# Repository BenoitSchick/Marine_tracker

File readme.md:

# 🌊 PI MONIT – Group 4  
## Marine Animal Tracking System  

**Schick Benoit · Warpelin Daryl · Jeyapalan Jeyapiragash · Zweifel Robin**

---

## 📌 Project Overview

This project focuses on the design of an embedded tracking module intended to be attached to marine animals.

The primary objective is to monitor animal movements in order to:

- Better understand behavioural patterns  
- Analyse migratory routes  
- Identify critical marine areas requiring protection  

Beyond behavioural research, marine animals provide a unique and valuable platform for carrying environmental sensors. Their ability to travel long distances and dive to great depths enables data collection in regions that are difficult — or impossible — for humans to access.

Our system is designed to measure **ocean temperature as a function of depth**, contributing to climate research. Ocean temperature plays a crucial role in regulating ocean currents, which in turn significantly influence the planet’s global thermal balance.

The device must satisfy both **animal tracking** and **oceanographic measurement** requirements, while operating reliably under extreme marine conditions.

---

## 🌊 Mechanical & Environmental Constraints

The module must withstand harsh deep-sea conditions for extended periods.

### Pressure Resistance

- Fully waterproof housing  
- Designed to resist pressures equivalent to **1,000 m depth** (to be confirmed)  
- Some marine species dive beyond 1,000 m  

### Corrosion & Environmental Resistance

- Long-term exposure to seawater  
- Resistance to:
  - Salinity  
  - Thermal variations  
  - Biological fouling  

### Duration

- Minimum operational lifespan: **1 month**  
- Corresponds to a typical migration cycle  

### Structural Integrity

- Housing must maintain mechanical integrity despite:
  - High pressure  
  - Temperature changes  
  - Continuous environmental stress  

---

## ⚡ Electronic Constraints & Specifications

The embedded system must operate autonomously for at least **one month**.

### Power Optimization Strategy

- Optimised electronic architecture  
- Deep sleep operating modes  
- Careful selection of ultra-low-power components  

### Required Sensors

The module must integrate:

- 🌡️ **Temperature sensor**  
- 📏 **Pressure sensor** (for depth measurement and data validation)

These measurements form the foundation of the ocean monitoring component of the project.

---

## 📍 Localisation System

A GPS module must be integrated to:

- Track the animal’s position  
- Associate environmental measurements with precise geographic coordinates  

Position data is essential for accurate mapping and scientific analysis.

---

## 📡 Data Communication

When the animal surfaces, the module must transmit collected data.

Because the system operates in open ocean environments, communication must be achieved via:

- 🛰️ **Satellite link** (global coverage solution)

The transmitted data is then:

- Stored in a central database  
- Prepared for processing and analysis  

---

## 📊 Data Processing & Visualisation

Collected data will be:

1. Processed and validated  
2. Made accessible via a web platform  
3. Presented through interactive visualisations  

The platform must also:

- Provide access to raw scientific data  
- Enable collaboration within the research community  

The final repository could be based on the EMODnet portal  
(European Marine Observation and Data Network).

---

## 🎯 Project Goals Summary

- ✔ Long-term autonomous marine monitoring  
- ✔ Behavioural tracking of marine species  
- ✔ Ocean temperature profiling by depth  
- ✔ Satellite-based data transmission  
- ✔ Open scientific data access  
- ✔ Contribution to climate research  

---

> PI MONIT aims to combine embedded systems engineering, oceanography, and data science to support marine conservation and climate research.

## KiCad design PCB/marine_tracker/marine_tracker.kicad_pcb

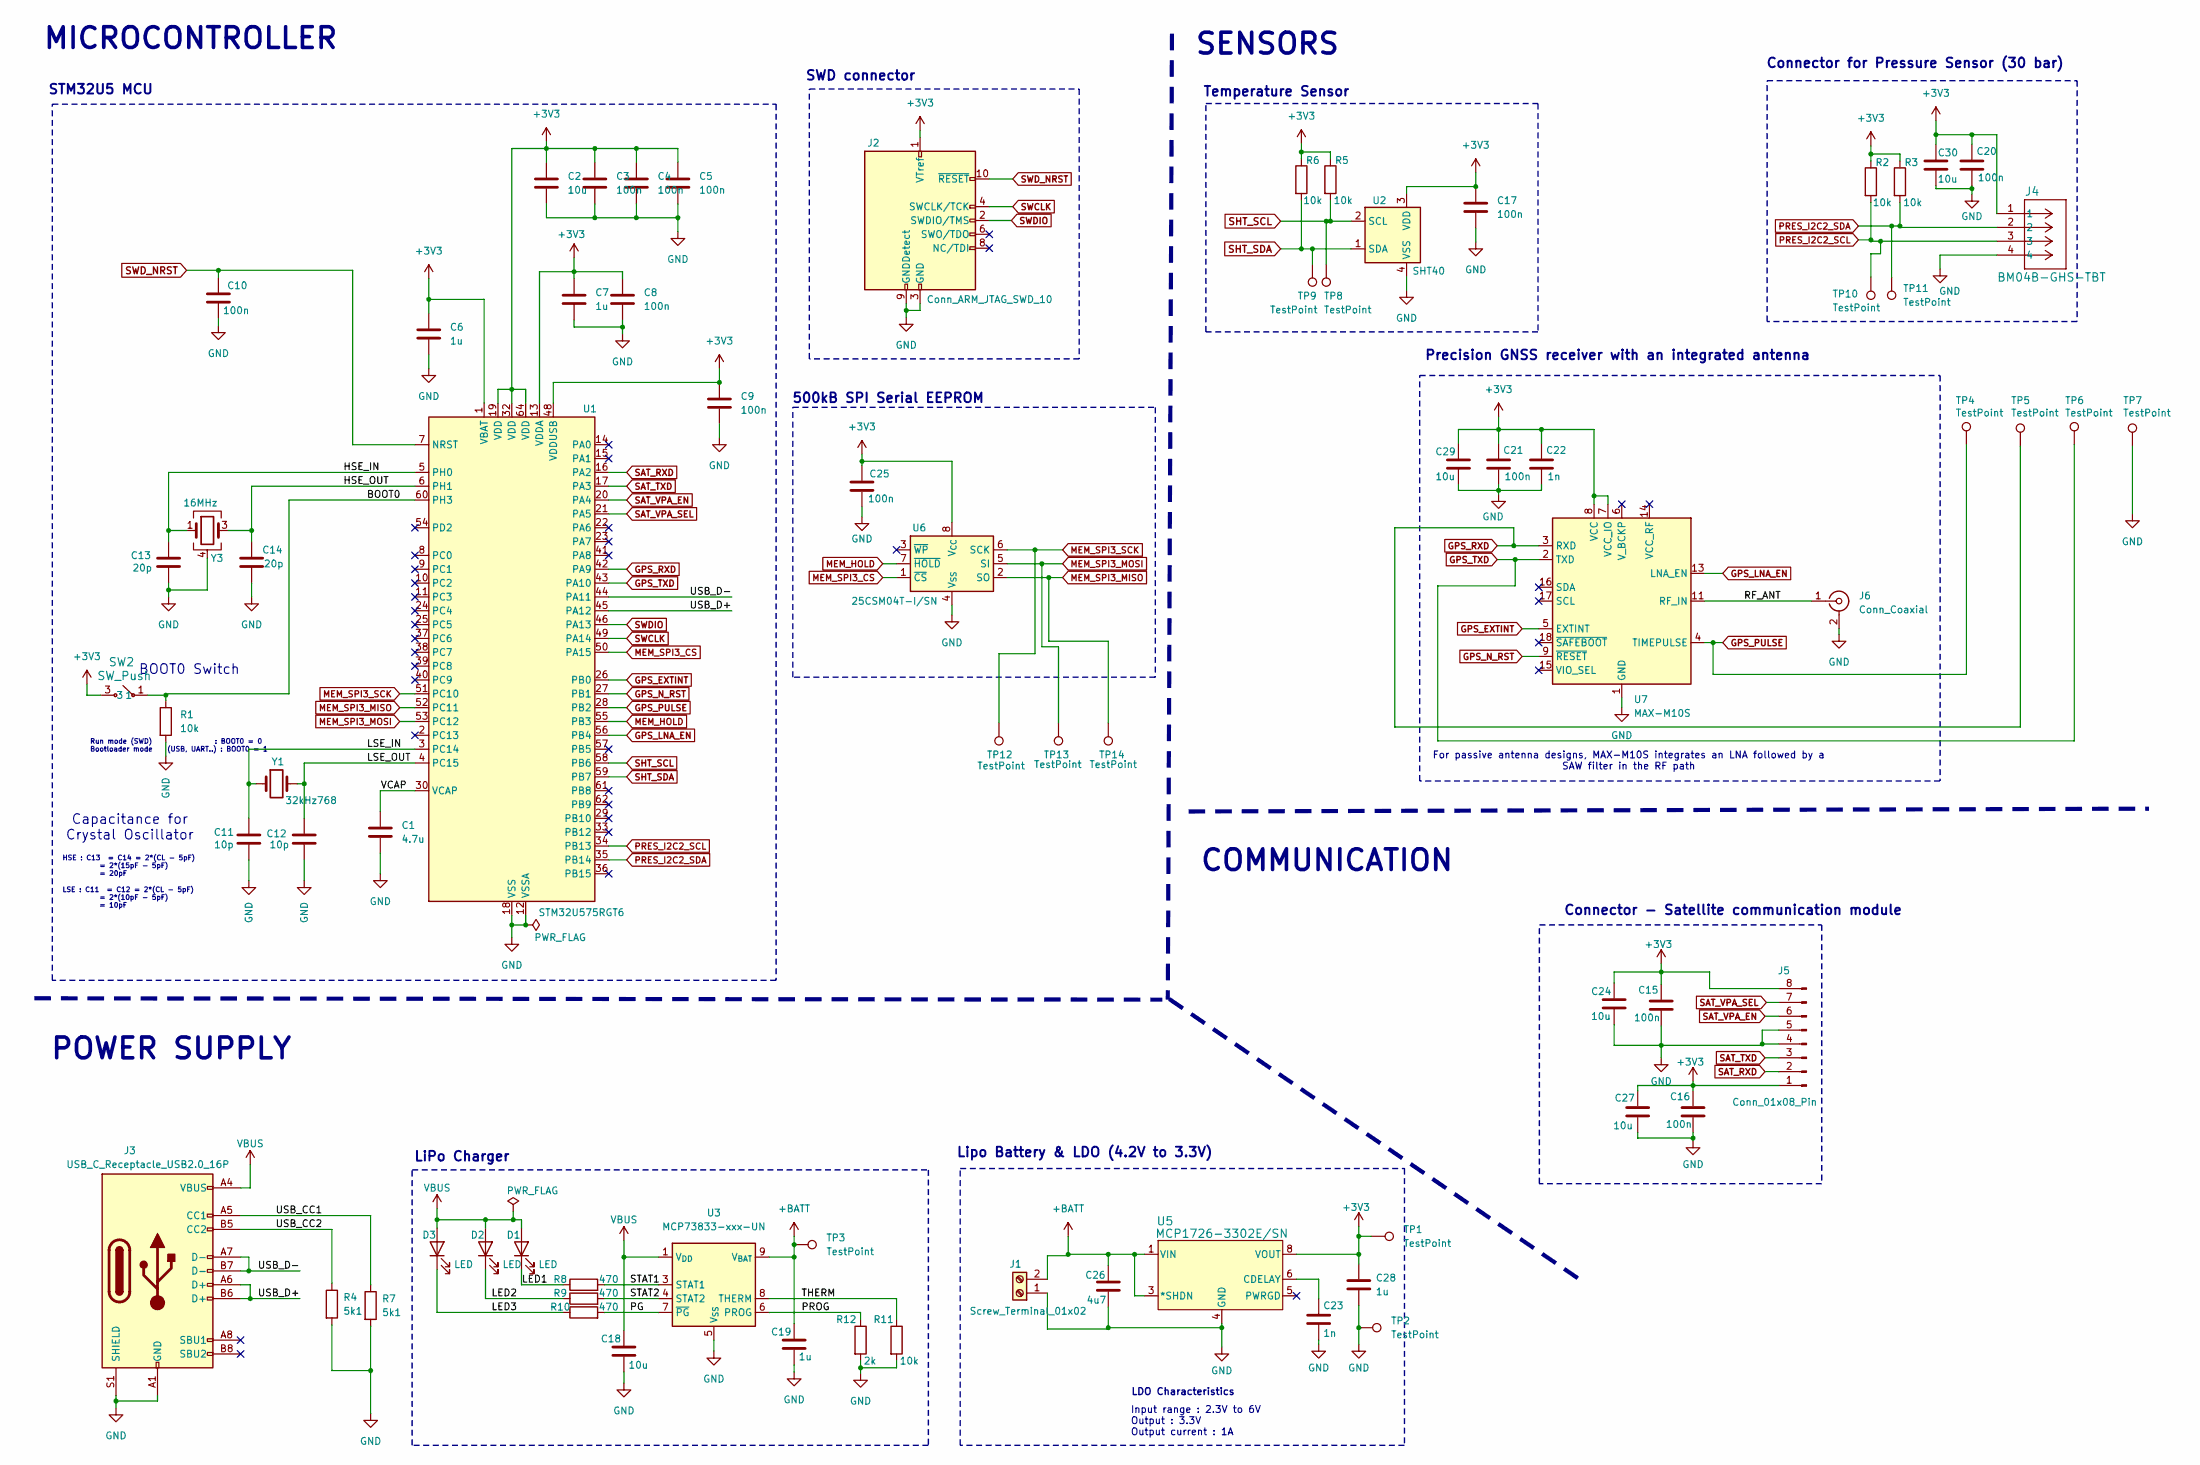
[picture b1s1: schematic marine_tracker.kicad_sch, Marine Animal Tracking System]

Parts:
C1: 4.7u; C_0805_2012Metric; Manufacturer Part Number CC0805ZKY5V7BB475; Digikey Part Number 311-1907-2-ND
C2, C18, C24, C27, C29, C30: 10u; C_0805_2012Metric; Manufacturer Part Number CC0805KRX5R7BB106; Digikey Part Number 311-3502-2-ND
C3, C4, C5, C8, C9, C10, C15, C16, C17, C20, C21, C25: 100n; C_0603_1608Metric; Manufacturer Part Number CC0603KRX7R7BB104; Digikey Part Number 311-1088-2-ND
C6, C7, C19, C28: 1u; C_0603_1608Metric; Manufacturer Part Number CC0603KRX7R7BB105; Digikey Part Number 311-1446-2-ND
C11, C12: 10p; C_0603_1608Metric; Manufacturer Part Number CC0603JRNPO9BN100; Digikey Part Number 311-1058-2-ND
C13, C14: 20p; C_0603_1608Metric; Manufacturer Part Number CC0603JRNPO0BN200; Digikey Part Number 311-1754-2-ND
C22, C23: 1n; C_0603_1608Metric; Manufacturer Part Number CC0603JPNPO9BN102; Digikey Part Number 13-CC0603JPNPO9BN102TR-ND
C26: 4u7; C_0603_1608Metric; Manufacturer Part Number CC0603KRX5R7BB475; Digikey Part Number 311-1785-2-ND
D1, D2, D3: LED; LED_0603_1608Metric; Manufacturer Part Number SML-D12U1WT86; Digikey Part Number SML-D12U1WT86TR-ND
J1: Screw_Terminal_01x02; Screw_terminal_1x2; Manufacturer Part Number 691137710002; Digikey Part Number 732-10955-ND
J2: Conn_ARM_JTAG_SWD_10; PinHeader_2x05_P1.27mm_Vertical; Manufacturer Part Number 20021111-00010T4LF; Digikey Part Number 609-3712-ND
J3: USB_C_Receptacle_USB2.0_16P; USB_C_Receptacle_GCT_USB4105-xx-A_16P_TopMnt_Horizontal; Manufacturer Part Number USB4215-03-A; Digikey Part Number 2073-USB4215-03-ATR-ND
J4: BM04B-GHS-TBT; CONN_BM04B-GHS-TBT_JST; Manufacturer Part Number BM04B-GHS-TBT; Digikey Part Number 455-BM04B-GHS-TBTTR-ND
J5: Conn_01x08_Pin; PinHeader_1x08_P2.54mm_Vertical; Manufacturer Part Number 61300811121; Digikey Part Number 732-5321-ND
J6: Conn_Coaxial; CONN_UFL_RSP-122811-01_SAI; Manufacturer Part Number RSP-122811-01; Digikey Part Number 612-RSP-122811-01TR-ND
R1, R2, R3, R5, R6, R11: 10k; R_0402_1005Metric; Manufacturer Part Number RC0402FR-0710KL; Digikey Part Number 311-10.0KLRTR-ND
R4, R7: 5k1; R_0402_1005Metric; Manufacturer Part Number RC0402FR-075K1L; Digikey Part Number 311-5.10KLRTR-ND
R8, R9, R10: 470; R_0402_1005Metric; Manufacturer Part Number RC0402FR-07470RL; Digikey Part Number 311-470LRTR-ND
R12: 2k; R_0402_1005Metric; Manufacturer Part Number RC0402FR-072KL; Digikey Part Number 311-2KLRTR-ND
SW2: SW_Push; SW4_PTS815 SJM 250 SMTR LFS_CNK_btnPoussoir; Manufacturer Part Number PTS815SJM250SMTRLFS; Digikey Part Number CKN12215-2-ND
TP1, TP2, TP3, TP8, TP9, TP12, TP13, TP14: TestPoint; TestPoint_Pad_D1.0mm
TP4, TP5, TP6, TP7, TP10, TP11: TestPoint; PinHeader_1x01_P2.54mm_Vertical
U1: STM32U575RGT6; LQFP-64_10x10mm_P0.5mm; Manufacturer Part Number STM32U575RGT6; Digikey Part Number 497-STM32U575RGT6-ND
U2: SHT40; Sensirion_DFN-4_1.5x1.5mm_P0.8mm_SHT4x_NoCentralPad; Manufacturer Part Number SHT40-AD1B-R3; Digikey Part Number 1649-SHT40-AD1B-R3TR-ND
U3: MCP73833-xxx-UN; lipo_charger; Manufacturer Part Number MCP73833T-FCI/MF; Digikey Part Number MCP73833T-FCI/MFTR-ND
U5: MCP1726-3302E/SN; LDO_1A; Manufacturer Part Number MCP1726-3302E/MF; Digikey Part Number MCP1726-3302E/MF-ND
U6: 25CSM04T-I/SN; JEITA_SOIC-8_3.9x4.9mm_P1.27mm; Manufacturer Part Number 25CSM04T-I/SN; Digikey Part Number 150-25CSM04T-I/SNTR-ND
U7: MAX-M10S; ublox_MAX; Manufacturer Part Number MAX-M10S-00B; Digikey Part Number 672-MAX-M10S-00BTR-ND
Y1: 32kHz768; Crystal_SMD_3215-2Pin_3.2x1.5mm; Manufacturer Part Number FC-135R 32.7680KA-A3; Digikey Part Number SER4071TR-ND
Y3: 16MHz; Crystal_SMD_5032-4Pin_5.0x3.2mm; Manufacturer Part Number X1G0044510002; Digikey Part Number SER4396TR-ND

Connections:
+3V3: C2.1, C3.1, C4.1, C5.1, C6.1, C7.1, C8.1, C9.1, C15.1, C16.1, C17.1, C20.1, C21.1, C22.1, C24.1, C25.1, C27.1, C28.1, C29.1, C30.1, J2.1 (VTref), J4.1, J5.1, J5.8, R2.1, R3.1, R5.1, R6.1, SW2.3, SW2.4, TP1.1, U1.1 (VBAT), U1.13 (VDDA), U1.19 (VDD), U1.32 (VDD), U1.48 (VDDUSB), U1.64 (VDD), U2.3 (VDD), U5.7 (VOUT), U5.8 (VOUT), U6.8 (V_{CC}), U7.7 (VCC_IO), U7.8 (VCC)
+BATT: C19.1, C26.1, J1.2, TP3.1, U3.9 (V_{BAT}), U3.10 (V_{BAT}), U5.1 (VIN), U5.2 (VIN), U5.3 (*SHDN)
/BOOT0: R1.1, SW2.1, SW2.2, U1.60 (PH3)
/HSE_IN: C13.2, U1.5 (PH0), Y3.1
/HSE_OUT: C14.2, U1.6 (PH1), Y3.3
/LED1: D1.1 (K), R8.1
/LED2: D2.1 (K), R9.1
/LED3: D3.1 (K), R10.1
/LSE_IN: C11.2, U1.3 (PC14), Y1.1
/LSE_OUT: C12.2, U1.4 (PC15), Y1.2
/PG: R10.2, U3.7 (~PG)
/PROG: R12.1, U3.6 (PROG)
/RF_ANT: J6.1 (In), U7.11 (RF_IN)
/STAT1: R8.2, U3.3 (STAT1)
/STAT2: R9.2, U3.4 (STAT2)
/THERM: R11.1, U3.8 (THERM)
/USB_CC1: J3.A5 (CC1), R7.1
/USB_CC2: J3.B5 (CC2), R4.1
/USB_D+: J3.A6 (D+), J3.B6 (D+), U1.45 (PA12)
/USB_D-: J3.A7 (D-), J3.B7 (D-), U1.44 (PA11)
/VCAP: C1.1, U1.30 (VCAP)
GND: C1.2, C2.2, C3.2, C4.2, C5.2, C6.2, C7.2, C8.2, C9.2, C10.2, C11.1, C12.1, C13.1, C14.1, C15.2, C16.2, C17.2, C18.2, C19.2, C20.2, C21.2, C22.2, C23.2, C24.2, C25.2, C26.2, C27.2, C28.2, C29.2, C30.2, J1.1, J2.3 (GND), J2.5 (GND), J2.9 (GNDDetect), J3.A1 (GND), J3.A12 (GND), J3.B1 (GND), J3.B12 (GND), J3.S1 (SHIELD), J4.4, J5.4, J5.5, J6.2 (Ext), J6.3 (Ext2), R1.2, R4.2, R7.2, R11.2, R12.2, TP2.1, TP7.1, U1.12 (VSSA), U1.18 (VSS), U1.31 (VSS), U1.47 (VSS), U1.63 (VSS), U2.4 (VSS), U3.5 (V_{SS}), U3.11 (EP), U5.4 (GND), U5.9 (EP), U6.4 (V_{SS}), U7.1 (GND), U7.10 (GND), U7.12 (GND), Y3.2, Y3.4 (G)
GPS_EXTINT: U1.26 (PB0), U7.5 (EXTINT)
GPS_LNA_EN: U1.56 (PB4), U7.13 (LNA_EN)
GPS_N_RST: U1.27 (PB1), U7.9 (~RESET)
GPS_PULSE: TP4.1, U1.28 (PB2), U7.4 (TIMEPULSE)
GPS_RXD: TP5.1, U1.42 (PA9), U7.3 (RXD)
GPS_TXD: TP6.1, U1.43 (PA10), U7.2 (TXD)
MEM_HOLD: U1.55 (PB3), U6.7 (~HOLD)
MEM_SPI3_CS: U1.50 (PA15), U6.1 (~CS)
MEM_SPI3_MISO: TP14.1, U1.52 (PC11), U6.2 (SO)
MEM_SPI3_MOSI: TP13.1, U1.53 (PC12), U6.5 (SI)
MEM_SPI3_SCK: TP12.1, U1.51 (PC10), U6.6 (SCK)
unnamed: C23.1, U5.6 (CDELAY)
PRES_I2C2_SCL: J4.3, R2.2, TP10.1, U1.34 (PB13)
PRES_I2C2_SDA: J4.2, R3.2, TP11.1, U1.35 (PB14)
SAT_RXD: J5.2, U1.16 (PA2)
SAT_TXD: J5.3, U1.17 (PA3)
SAT_VPA_EN: J5.6, U1.20 (PA4)
SAT_VPA_SEL: J5.7, U1.21 (PA5)
SHT_SCL: R5.2, TP8.1, U1.58 (PB6), U2.2 (SCL)
SHT_SDA: R6.2, TP9.1, U1.59 (PB7), U2.1 (SDA)
SWCLK: J2.4 (SWCLK/TCK), U1.49 (PA14)
SWDIO: J2.2 (SWDIO/TMS), U1.46 (PA13)
SWD_NRST: C10.1, J2.10 (~RESET), U1.7 (NRST)
VBUS: C18.1, D1.2 (A), D2.2 (A), D3.2 (A), J3.A4 (VBUS), J3.A9 (VBUS), J3.B4 (VBUS), J3.B9 (VBUS), U3.1 (V_{DD}), U3.2 (V_{DD})

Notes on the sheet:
SWD connector
Lipo Battery & LDO (4.2V to 3.3V)
HSE : C13 = C14 = 2*(CL - 5pF) = 2*(15pF - 5pF) = 20pF
LSE : C11 = C12 = 2*(CL - 5pF) = 2*(10pF - 5pF) = 10pF
Precision GNSS receiver with an integrated antenna
POWER SUPPLY
STM32U5 MCU
Capacitance for Crystal Oscillator
SENSORS
LDO Characteristics
LiPo Charger
COMMUNICATION
For passive antenna designs, MAX-M10S integrates an LNA followed by a SAW filter in the RF path
MICROCONTROLLER
BOOT0 Switch
Connector - Satellite communication module
Run mode (SWD) : BOOT0 = 0 Bootloader mode (USB, UART..) : BOOT0 = 1
Input range : 2.3V to 6V Output : 3.3V Output current : 1A
500kB SPI Serial EEPROM
Connector for Pressure Sensor (30 bar)
Temperature Sensor

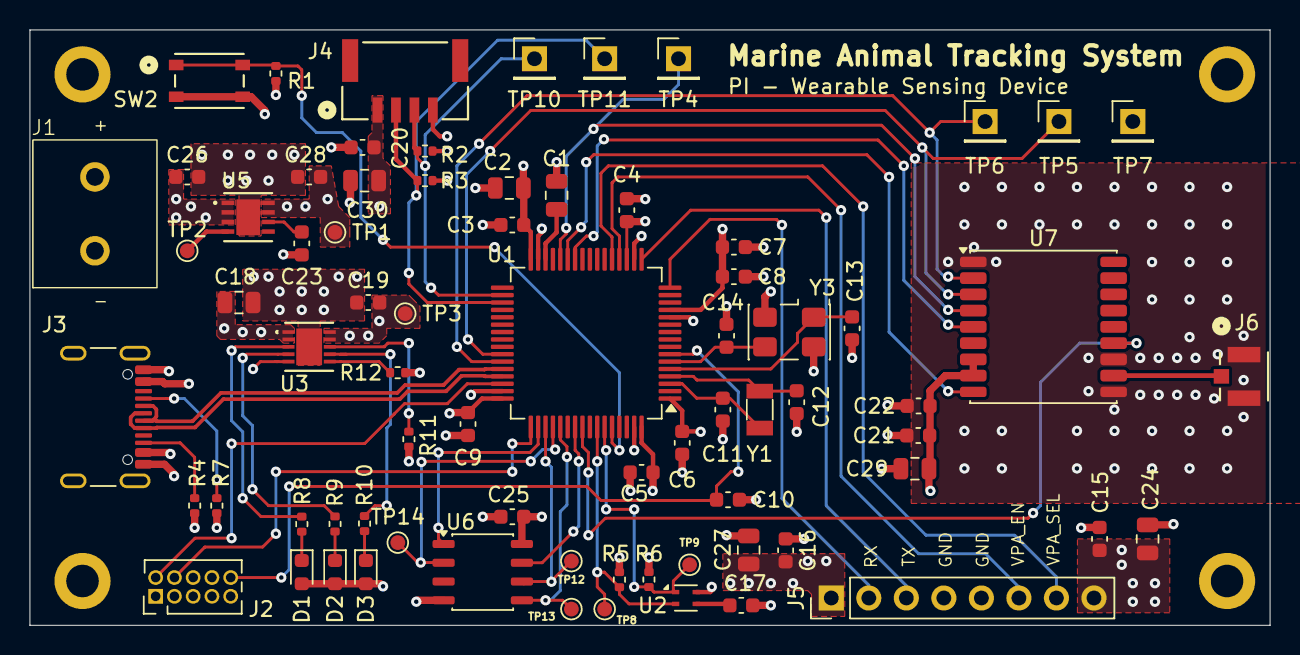
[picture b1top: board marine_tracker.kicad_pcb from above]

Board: 4 copper layers, 83.9 x 40.3 mm, 74 parts (0 on the bottom side), 46 nets.

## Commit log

2026-02-27 STM32 Schematic finished
2026-03-01 update schematics
2026-03-01 schematics update
2026-03-05 add screw terminal for battery
2026-03-05 add new connector for pressure sensor
2026-03-05 add connector for satellite communication module
2026-03-05 add 3D models
2026-03-06 Component Placement + export Step file PCB
2026-03-19 routage + change GNSS module + add decoupling capacitor + change 0200/0400 package to 0600 package
2026-03-19 PCB routage WIP
2026-03-23 add new connector for Satellite module + new LDO regulator with an maximum current higher
2026-03-26 change to UFL connector + add stiching via
2026-03-26 drc violation PCB corrected
2026-03-29 add reference to symbols
2026-03-31 correction PCB
2026-03-31 PCB finish
2026-03-31 adapt silkscreen
2026-04-02 final review + add part number
2026-04-02 resolve DRC violation
2026-04-03 adding testpoint
2026-04-23 add report
2026-04-30 writting report
2026-04-30 add files
2026-04-30 update .gitignore latex project
2026-04-30 remove useless files
2026-04-30 report WIP
2026-05-06 measure GPS antenna
2026-05-07 gnss part - report
2026-05-08 report : GNSS and antenna part done
2026-05-08 calcul consommation in progress
2026-05-10 consommation part done
2026-05-14 rapport final PI
2026-05-14 pdf report
